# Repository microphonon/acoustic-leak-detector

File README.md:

# acoustic-leak-detector

## Features
- Stand-off detection of small water leaks, even behind walls
- Designed for high sensitivity, reliability, and long battery life
- In-situ analysis – no audio streamed to cloud
- Smart Sensing
  - Nominal acoustic background acquired at startup
  - Statistical analysis distinguishes environmental noise
  - Impulse noise rejection
  - Eavesdropping impossible

- Two-way communication with host controller via I2C
  - Detailed sensor status available on demand
  - Sensing parameters highly configurable by host
  - Immediate notification with leak and noise alert interrupts

- Based on the Texas Instruments MSP430FR5994 MCU
  - FFT spectral analysis > 10x faster, more efficient than ARM-Cortex M0+
  - Direct Memory Access moves data without CPU intervention
  - Sensor operational voltage range: 1.8–3.6V

Specifications and complete details are in the comprehensive . An academic paper that describes the device design and performance is available at [arXiv.org](https://arxiv.org/abs/2511.00348). 

In this repository you will find:

- Design documentation, schematics, PCB layout, and firmware
- Stand-alone graphical user interface for a PC using [Arduino](https://store-usa.arduino.cc/products/arduino-nano-33-iot), [Raspberry Pi](https://www.raspberrypi.com/products/raspberry-pi-pico/), or [I2CDriver](https://i2cdriver.com/) as intermediary hardware for I2C communication
- Firmware for two-way text-based communication using the terminal
- Demonstration of sensor integration with Home Assistant using [ESPHome](https://devices.esphome.io/devices/aquaping/)  

A sensor board called AquaPing with pre-loaded firmware is available for purchase at [Mouser](https://www.mouser.com/ProductDetail/MicroPhonon/CS-AQUAPING-01?qs=IPgv5n7u5QZ96LnbcZcGBA%3D%3D) and  [Crowd Supply](https://www.crowdsupply.com/microphonon/aquaping). This is an open-hardware project.

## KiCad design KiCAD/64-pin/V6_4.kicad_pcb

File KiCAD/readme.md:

# KiCAD files
There are two versions of the PCB for designs using either a 48- or 64-pin MSP430FR5994 microcontroller. Both the schematic and layout KiCAD files use some custom components. These are probably already available online somewhere, but I decided to make my own 
footprints following the manufacturer data sheets to reduce the risk of fabrication problems.

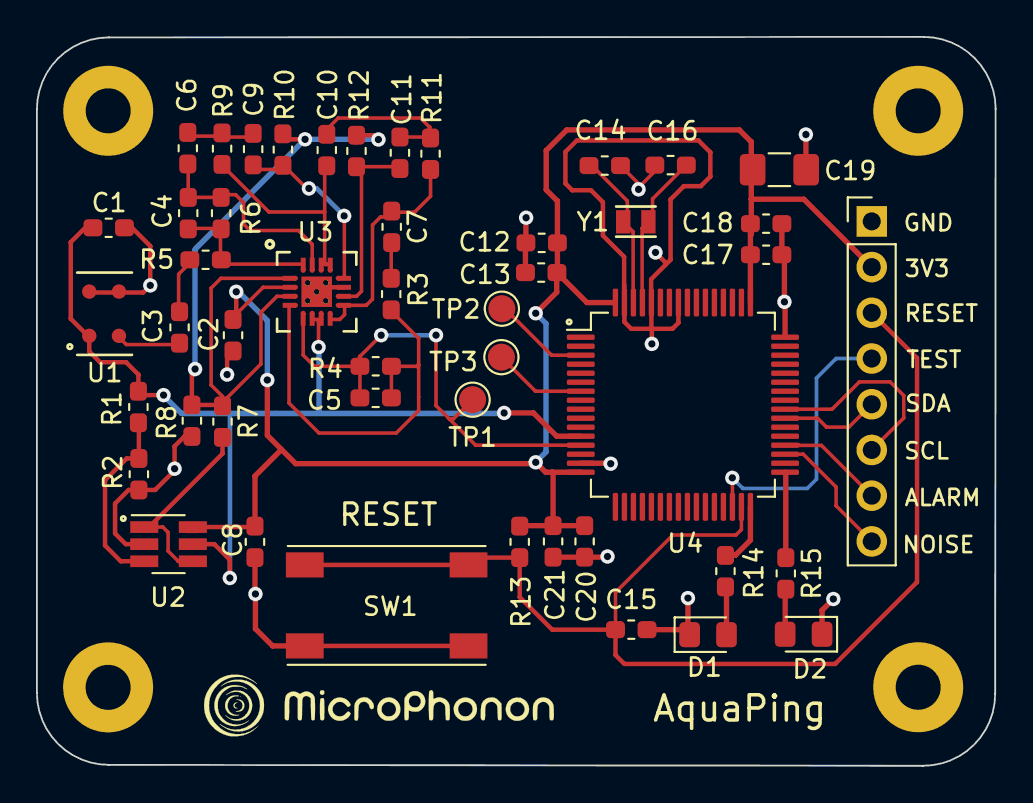
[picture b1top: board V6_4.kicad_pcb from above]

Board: 2 copper layers, 53.3 x 40.5 mm, 52 parts (0 on the bottom side), 33 nets.

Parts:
C1, C2, C3, C7, C8, C13, C17, C21: 100n; C_0603_1608Metric_Pad1.05x0.95mm_HandSolder
C4: 100p; C_0603_1608Metric_Pad1.05x0.95mm_HandSolder
C5: 470p; C_0603_1608Metric_Pad1.05x0.95mm_HandSolder
C6: 15n; C_0603_1608Metric_Pad1.05x0.95mm_HandSolder
C9: 4.7n; C_0603_1608Metric_Pad1.05x0.95mm_HandSolder
C10: 150n; C_0603_1608Metric_Pad1.05x0.95mm_HandSolder
C11: 47n; C_0603_1608Metric_Pad1.05x0.95mm_HandSolder
C12, C18, C20: 1u; C_0603_1608Metric_Pad1.05x0.95mm_HandSolder
C14, C16: 22p; C_0603_1608Metric_Pad1.05x0.95mm_HandSolder
C15: 1n; C_0603_1608Metric_Pad1.05x0.95mm_HandSolder
C19: 10u; C_1206_3216Metric_Pad1.42x1.75mm_HandSolder
D1: GREEN; D_0805_2012Metric_Pad1.15x1.40mm_HandSolder
D2: RED; D_0805_2012Metric_Pad1.15x1.40mm_HandSolder
H1, H2, H3, H4: MountingHole; MountingHole_2.5mm_Pad
J1: Conn_01x08; PinHeader_1x08_P2.54mm_Vertical
R1, R2, R8, R13: 47k; R_0603_1608Metric_Pad1.05x0.95mm_HandSolder
R3, R5: 1k; R_0603_1608Metric_Pad1.05x0.95mm_HandSolder
R4: 15k; R_0603_1608Metric_Pad1.05x0.95mm_HandSolder
R6: 100k; R_0603_1608Metric_Pad1.05x0.95mm_HandSolder
R7: 10; R_0603_1608Metric_Pad1.05x0.95mm_HandSolder
R9: 620; R_0603_1608Metric_Pad1.05x0.95mm_HandSolder
R10, R12: 2k; R_0603_1608Metric_Pad1.05x0.95mm_HandSolder
R11: 30; R_0603_1608Metric_Pad1.05x0.95mm_HandSolder
R14, R15: 470; R_0603_1608Metric_Pad1.05x0.95mm_HandSolder
SW1: Reset; TS04
TP1, TP2, TP3: TEST; TestPoint_Pad_D1.5mm
U1: SPU0410; SPU0410H
U2: TLV9061S; SOT-23-6_Handsoldering
U3: TLV9064S
U4: MSP430FR5994_64pin; LQFP-64_10x10mm_P0.5mm
Y1: ECX-12R

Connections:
3.3V: C2.2, C8.1, C12.2, C13.2, C17.1, C18.1, C19.1, C20.2, C21.2, J1.2, R13.1, U2.6, U3.2, U4.16, U4.49, U4.64
GND: C1.1, C2.1, C8.2, C12.1, C13.1, C14.2, C15.2, C16.1, C17.2, C18.2, C19.2, C20.1, C21.1, D1.1, D2.1, J1.1, R2.2, R8.2, SW1.1, U1.2, U1.3, U2.2, U3.11, U3.17, U4.15, U4.48, U4.57, U4.60, U4.63
unnamed: C1.2, R1.1, U1.1, U2.5, U3.6, U3.7, U4.12
unnamed: C3.1, R5.2
unnamed: C3.2, U1.4
unnamed: C4.1, C6.2, R6.1, U3.15
unnamed: C4.2, R5.1, R6.2, U3.16
unnamed: C5.1, R3.2, R4.1, U3.4
unnamed: C5.2, R4.2, TP1.1, U3.5, U4.13
unnamed: C6.1, C9.2, R9.2
unnamed: C7.1, R11.2, U3.8, U3.9
unnamed: C7.2, R3.1
unnamed: C9.1, R10.2, U3.12
unnamed: C10.1, C11.2, R11.1
unnamed: C10.2, R9.1, U3.13, U3.14
unnamed: C11.1, R12.2, U3.10
unnamed: C14.1, U4.62, Y1.1
unnamed: C15.1, J1.3, R13.2, SW1.2, U4.31
unnamed: C16.2, U4.61, Y1.2
unnamed: D1.2, R14.2
unnamed: D2.2, R15.2
unnamed: J1.4, U4.30
unnamed: J1.5, U4.39
unnamed: J1.6, U4.40
unnamed: J1.7, U4.36
unnamed: J1.8, U4.35
unnamed: R1.2, R2.1, U2.3
unnamed: R7.2, U2.1, U2.4
unnamed: R14.1, U4.32
unnamed: R15.1, U4.33
unnamed: TP2.1, U4.3
unnamed: TP3.1, U4.7
VGND: R7.1, R8.1, R10.1, R12.1, U3.1, U3.3

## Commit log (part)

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2022-04-04 Create KiCAD
2022-04-04 Rename V6_3.kicad_pcb to FFT_layout.kicad_pcb
2022-04-04 Rename V6_3.sch to FFT_schematic.sch
2022-04-04 Create test
2022-04-08 Add files via upload
    AquaPing interfaced with a Lolin D1-mini WiFi module via I2C. The host PC can also send commands and receive data via a terminal program. This is done through the USB-UART interface on the D1-mini, w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
2022-04-10 Add files via upload
    Fixed bug that forced entry into sleep mode when LEDs instructed to turn off. Now firmware version 37
2022-04-10 Add files via upload
    Fixed some small bugs.
2022-04-10 Rename Example_code/readme.md to ESP8266 modules/test.md
2022-04-12 Add files via upload
    D1_mini.ino modified to upload data to ThingSpeak network.
2022-04-15 Add files via upload
    Cleanup the code. Now at version 38
2022-04-17 Add files via upload
    A few minor edits
2022-04-18 Add files via upload
    Populated board before adding thru-hole and resonator
2022-04-23 Upload user manual version 0.5
2022-04-23 Small edits to firmware Version 38
2022-04-24 Minor edits to User Manual version 0.5
2022-04-24 Edits to User Manual version 0.5
2022-04-26 User manual version 0.6
2022-04-27 Edited the comments
2022-04-28 Add some text and sound collection directivity
2022-05-05 Create LICENSE
2022-05-07 Firmware version 39.
    Don't clear counts when the LED state is toggled. There is no need to re-acquire a data set if the user decides to turn off the LEDs.
2022-05-07 User manual version 0.7
2022-05-11 Cleaned up the code. Firmware version 40
2022-05-14 Revised Gerber files
2022-05-14 Rename V6_3.kicad_pcb to layout.kicad_pcb
2022-05-14 Rename V6_3.sch to schematic.sch
2022-05-23 User manual version 0.8
2022-05-24 Code cleanup. Firmware version 41
2022-06-14 More code cleanup; Firmware version 42
2022-06-21 Minor edits; Firmware version 42
2022-07-09 Setup counting as an array of structures; ver 43
2022-07-10 Boolean flags; version 44
2022-07-11 Version 0.9 with Quick Start info
2022-07-12 Minor edits
2022-07-19 Firmware ver 24. Improved energy use
2022-07-19 Firmware version 45
2022-07-19 User manual version 0.10
2022-07-20 Edits to user manual version 0.10
2022-08-08 Firmware version 46
    Better management of low-power. Keep timer TA1 off until it is needed
2022-08-10 Out-of-box demo video
    This short .mp4 shows the AquaPing in monitor mode powered by 2 x AAA batteries. LEDs blink in response to the acoustics. Details in the User Manual.
2022-08-14 User Guide v0.11
2022-08-22 Add troubleshooting section to User Manual v0.12
2022-08-24 Background acquisition signaled by LEDs
2022-08-24 User manual version 0.13
2022-09-29 Rename V6_4.kicad_pcb to 64pin.kicad_pcb
2022-09-29 Rename V6_4.sch to 64pin.sch
2022-09-29 Rename KiCAD/layout.kicad_pcb to KiCAD/48-pin/48pin.kicad_pcb
2022-09-29 Rename KiCAD/schematic.sch to KiCAD/48-pin/48pin.sch
2022-09-29 Rename firmware/main.c to firmware/48-pin/main.c
2022-09-30 Rename FFT_symbols.dcm to AquaPing_symbols.dcm
2022-09-30 Rename FFT_symbols.lib to AquaPing_symbols.lib
2022-10-07 version 0.15
2022-10-13 Create junk
2022-10-26 Version 47
    Minor edit to reset digital alert pins at the start of a training session
2022-10-26 User manual version 0.16
2022-10-28 User manual v 0.17
2022-10-28 User manual 0.17 update
    Edits to the Troubleshooting section
2022-10-28 Edits to the troubleshooting section
2022-10-30 User manual ver 0.18
    Incorporates changes implemented in firmware version 48
2022-10-30 Firmware version 48
2022-10-30 Minor edit to ver 48
2022-11-05 Ver 48 minor bug fix
2022-11-07 formatting
2022-11-11 Edited user manual v0.18
2022-11-11 Minor edits user manual 0.18
2022-11-16 User manual ver 0.19
    Added electrical specifications
2022-11-16 User manual v 0.19
    Fixed typo
2022-11-16 Minor edits user manual ver 0.19
2022-11-22 Fixed a couple of typos is user manual
2022-11-30 User manual version 0.20
    Just some minor revisions. Added copyright and some clarifying text
2022-11-30 Fixed typo version 0.20
2022-12-14 User manual ver 0.20; minor edits
2023-01-11 Firmware version 49
    Alternate version of the code that uses more efficient ring buffers for the counting arrays. Saves CPU cycles but may not have noticeable effect on battery life?
2023-01-17 Version 48 code cleanup
2023-01-17 Version 49 code cleanup
2023-01-17 Version 46 code cleanup
2023-01-26 New product banner
2023-01-26 Update brochure with curent image
2023-04-26 Global variable not needed in dashboard
2023-04-26 Global variable not needed
2023-05-25 Edit the read.me file to make it clearer
2023-05-29 Minor edit to Home Assistant readme.md
2023-06-01 Edit readme with troubleshooting tip
2023-06-04 Update readme.md
    Link to new page that describes how to interface a custom I2C sensor to the Home Assistant dashboard.
2023-08-28 Link to paper on Techrxiv
2026-01-15 Update README.md
    Fix formatting error on README.md
